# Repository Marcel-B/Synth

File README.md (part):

# Tonwerk Synth

Die beiden Browser-Synthesizer aus Tonwerk (YuE UI) als Plugins für Logic Pro: **Tonwerk Analog** und **Tonwerk FM**, jeder mit Delay und Hall und eigenen Werksklängen. Dazu kommen **Tonwerk DX** mit sechs Operatoren für den klassischen FM-Klang der Achtziger, der Wavetable-Synthesizer **Tonwerk Wavetable** für Dubstep-Bässe, der Granular-Synthesizer **Tonwerk Granular** für Klangwolken, **Tonwerk Physical**, der gezupfte, gestrichene, geblasene und angeschlagene Instrumente aus ihrer Physik nachrechnet, **Tonwerk Additiv**, der Klänge aus bis zu 64 einzelnen Obertönen zusammensetzt, **Tonwerk PD** mit Phasenverzerrung, der digitalen Synthese der Achtziger, der Sampler **Tonwerk Sampler** für eigene Samples, Loops und Vocal-Chops, **Tonwerk Bass**, ein Acid-Bass mit Slide und Accent, **Tonwerk Neuro**, ein monophoner Bass für Reese- und Neuro-Sounds aus Drum and Bass und Dubstep, **Tonwerk Expander**, ein achtstimmiger Analog-Synth nach Art der Expander-Module der Siebziger mit stufenlosem 12-dB-Multimode-Filter, die Drum-Machine **Tonwerk Groovebox** mit Step-Sequencer, **Tonwerk Drums**, ihre Klänge und acht weitere auf den Tasten der General-MIDI-Belegung, **Tonwerk Rig**, das eines dieser Instrumente mit bis zu sechs Effekten dahinter als einen Klang spielt, die Effekte **Chrome Glitch** für zerstückelte Gesangsspuren, **Tonwerk Distortion**, ein klassischer Gitarren-Verzerrer, **Tonwerk Robovox**, der eine Stimme wie einen Roboter singen lässt, **Tonwerk Vocoder**, der klassische Vocoder, bei dem die Stimme einen Synth spricht, den du mit Akkorden spielst, **Tonwerk Wobble**, Filter und Volume mit selbst gezeichneten LFO-Kurven im Tempo für Dubstep-Wobbles, **Tonwerk Tape**, eine leiernde, rauschende Bandmaschine für Lo-Fi, **Tonwerk Delay**, ein Ping-Pong-Delay im Songtempo mit Filtern im Feedback und Ducking, **Tonwerk Chorus**, Chorus, Ensemble, Flanger und Phaser in einem, **Tonwerk Glue**, ein Bus-Kompressor mit Sidechain und Pumpen im Songtempo, und **Tonwerk Shimmer**, ein Hall, dessen Fahne mit jedem Umlauf um ein Intervall nach oben steigt, **Tonwerk Filter**, ein Multimode-Filter mit Envelope Follower und LFO im Songtempo, **Tonwerk Stutter**, ein Beat Repeat, der Stücke im Songtempo wiederholt, **Tonwerk Multiband**, ein Drei-Band-Kompressor, abwärts und aufwärts, **Tonwerk Zone**, ein Kompressor für einen einstellbaren Frequenzbereich (dynamischer EQ, De-Esser), dessen Frequenz ein LFO wandern lassen kann, **Tonwerk Scope**, ein Oszilloskop mit Welle, Takten, Goniometer und Stimmgerät, **Tonwerk Rumble**, das aus der Kick selbst den rollenden Techno-Rumble darunter macht, **Tonwerk Reverb**, ein klassischer Hall mit Raum, Saal, Platte und Kathedrale, **Tonwerk Pump**, ein Sidechain-Compressor nur fürs Pumpen unter der Kick, **Tonwerk Spread**, der einen Klang aus der Mitte nach links und rechts verbreitert, ohne dass er in Mono etwas verliert, die MIDI-Effekte **Tonwerk Arp**, ein Arpeggiator und Step-Sequencer vor jedem Synth, und **Tonwerk LFO**, der per MIDI-Controller jeden Regler eines Tonwerk-Instruments bewegt (siehe unten). Klänge, die in Tonwerk auf der Instrumente-Seite gespeichert sind, lassen sich übernehmen und klingen hier wie dort.

**Sprache**: Alle Plugins und die App sprechen Deutsch oder Englisch. Auf einem deutschen System starten sie auf Deutsch, sonst auf Englisch. Der Schalter **DE | EN** oben im Fenster jedes Plugins wechselt die Sprache für alle Plugins zugleich; offene Fenster folgen nach spätestens einer Sekunde, die Knöpfe der iPad-App nach einem Neustart. Die Namen der Parameter in Logics Automation und im generischen Editor nehmen die Sprache beim Laden des Plugins an, also nach einem Neuladen des Projekts. Die Namen der Werksklänge bleiben deutsch, damit gespeicherte Projekte und Tonwerk Rig sie wiederfinden.

Logic lädt nur Audio Units, deshalb wird das Plugin als **Audio Unit** gebaut, dazu als VST3 (für andere Hosts) und als eigenständige App zum Ausprobieren ohne Logic.

## Zwei Plugins statt einem

Bis 0.3.0 waren beide Engines ein Plugin, **Tonwerk Synth**, mit einem Umschalter oben. Jetzt ist jede Engine ein eigenes Instrument: **Tonwerk Analog** (`aumu TwAn Bvlp`) und **Tonwerk FM** (`aumu TwFm Bvlp`). Jedes hat nur seine eigenen Regler (Logic zeigt bei der Automation also keine fremden mehr) und seine eigenen Werksklänge (siehe [Werksklänge](#werksklänge)).

Die aus Tonwerk oder Dateien übernommenen Klänge teilen sich beide Plugins (dieselbe `presets.json`); jedes zeigt im Menü nur die seiner Engine. Lädst du in Tonwerk Analog eine Datei mit FM-Klängen, landen sie im Menü von Tonwerk FM.

**Alte Projekte:** Tonwerk Synth bleibt installiert und lädt seine Projekte wie bisher, mit beiden Engines und den acht alten Werksklängen auf denselben Programmnummern (die neuen hängen dahinter). Es hat ebenfalls die neue Oberfläche. Für neue Spuren nimmst du Tonwerk Analog oder Tonwerk FM. Eine alte Spur ziehst du um, indem du in Tonwerk Synth **Speichern** drückst und die Datei im neuen Plugin mit **Datei laden** öffnest.

**Oberfläche:** alle Tonwerk-Plugins sehen jetzt aus wie Tonwerk Wavetable: fast schwarz, Gelb, Cyan und Rot im Neon-Look, Paneele mit abgeschnittener Ecke, Bildschirme mit Scanlines. Jede Hüllkurve zeigt ihre Form, Tonwerk FM zeichnet den gewählten Algorithmus (Träger gelb, Modulatoren cyan, die Rückkopplung an Operator 4) und schreibt über jede Operator-Hüllkurve, was der Operator gerade tut („TRÄGER“, „MOD → 1“). Werte stehen als ganze Zahlen mit Einheit da: Zeiten in ms, Pegel und Mengen in %, die Filter-Hüllkurve in Halbtönen (HT), langsame LFO-Raten mit einer Nachkommastelle.

## Was drin ist

**Analog**: zwei Oszillatoren (Sinus, Dreieck, Sägezahn, Rechteck/Puls) mit Oktave, Verstimmung und Pegel, Rauschen, Filter (Tiefpass, Hochpass, Bandpass) mit Resonanz, Keytracking und eigener Hüllkurve, Lautstärke-Hüllkurve, LFO auf Tonhöhe, Filter oder Lautstärke, frei oder im Songtempo. Der Puls hat eine Pulsbreite, die der LFO und beide Hüllkurven bewegen können (PWM).

**Wavefolder und Sample & Hold** gibt es nur im Plugin, nicht in Tonwerk. Der Wavefolder sitzt zwischen Oszillatoren und Filter. **Menge** treibt die Mischung bis zum Achtfachen und faltet alles über dem Vollpegel zurück, statt es abzuschneiden. **Symmetrie** verschiebt das Signal vor dem Falten, das bringt geradzahlige Obertöne. Mit **Hüllkurve** öffnet und schließt die Filter-Hüllkurve den Wavefolder. Sample & Hold nimmt in jedem Schritt einen neuen Zufallswert und hält ihn bis zum nächsten. **Filter** verschiebt damit den Cutoff um bis zu zwei Oktaven nach oben oder unten, **Tonhöhe** den Ton um bis zu eine Oktave. Das Tempo ist frei oder im Songtempo, und jede Note würfelt ihre eigene Folge. Beide stehen auf 0, solange du sie nicht aufdrehst, und Klänge aus Tonwerk laden mit beiden aus.

**FM**: vier Sinus-Operatoren in acht Algorithmen wie bei den 4-Operator-FM-Synths der Achtziger, Feedback auf Operator 4, eine Hüllkurve pro Operator, Anschlagsdynamik pro Operator, LFO auf Tonhöhe, Modulationsindex oder Lautstärke, frei oder im Songtempo.

**Effekte**: Delay mit Tiefpass in der Rückkopplung und Hall, beide als Send. Das Delay läuft frei oder im Songtempo.

**Tempo-Sync**: Mit **Sync** folgen LFO, Sample & Hold und Delay dem Tempo von Logic. Statt Hz oder Sekunden wählst du einen Notenwert von 4/1 bis 1/32, auch punktiert und triolisch. Ohne Host-Tempo (in der App) gelten 120 BPM. Der LFO beginnt wie in Tonwerk mit jeder Note neu. Er läuft also im Tempo, aber nicht auf den Schlag genau.

**Oszilloskop**: unten rechts neben der Tastatur, in beiden Plugins. Es zeigt die Wellenform dessen, was das Plugin gerade spielt, und steht bei einem gehaltenen Ton still.

16 Stimmen, Pitchbend ±2 Halbtöne, Sustain-Pedal. Jeder Regler ist ein Parameter, den Logic automatisieren kann und mit dem Projekt speichert. Jeder Drehregler lernt per Rechtsklick einen MIDI-Controller, etwa von [Tonwerk LFO](#tonwerk-lfo-midi-effekt-und-midi-lernen). Eine Tastatur unten im Fenster spielt das Plugin auch ohne MIDI-Keyboard an.

## Chrome Glitch (Effekt)

Ein Audio-Effekt aus demselben Repository, für eine Gesangsspur, deren „Sprach-Chrome“ versagt: Silben stottern („bo-bo-body“), die Stimme setzt kurz aus, wird digital zerbröselt und springt in der Tonhöhe. Er liegt in Logic unter **Audio-FX → Audio Units → b-velop → Chrome Glitch** und wird mit Tonwerk Synth zusammen gebaut, installiert und veröffentlicht.

Oben rechts sitzt ein kleiner **Monitor**: Solange die Stimme sauber ist, zeigt er „CHROME OK“. Bei jedem Glitch flimmert er mit zerrissenen Balken und Rauschen und zeigt „INTERFERENCE“ (Stottern), „NO SIGNAL“ (Aussetzer) oder „FROZEN“ (Einfrieren). Die Texte im Monitor sind bewusst englisch, wie die Anzeigen im Spiel. Auch Glitches, die kürzer als ein Bild sind, lassen ihn aufflackern.

Der Effekt arbeitet ohne Latenz auf dem, was gerade hereinkommt. An jedem Schritt des Rasters (im Songtempo) oder zu zufälligen Momenten (40–250 ms auseinander) würfelt er, ob etwas passiert:

- **Stottern**: Die letzten 10–200 ms (Standard 50 ms) werden mehrmals wiederholt. **Beschleunigen** macht jede Wiederholung kürzer, so wird die Silbe immer schneller. Ab der zweiten Wiederholung kann die Tonhöhe springen (**Pitch-Chance**, **Pitch-Bereich** bis ±24 Halbtöne).
- **Aussetzer**: Die Stimme fällt 20–300 ms ganz weg.
- **Bitcrusher**: Bei jedem Glitch voll (bis 4 Bit und 16-faches Downsampling), dazwischen nur leicht, mit der Stärke wachsend.
- **Einfrieren**: Hält die letzte Silbe in einer Schleife fest, solange es an ist. Für das letzte Wort, das hängen bleibt.
- **Tempo-Sync** und **Raster** (1/8, 1/16, 1/32) legen die Glitches aufs Raster. **Chaos** streut zusätzlich Glitches zwischen die Rasterpunkte und lässt die Stotterlänge schwanken, damit es nicht wie ein sauberer Stutter-Effekt klingt.
- **Glitch-Stärke** ist das Makro für die Automation: Auf 0 geht die Stimme unverändert durch, nach oben werden alle Chancen und der Crusher stärker. Für den letzten Chorus also die Stärke über die vier Zeilen hochziehen und am Ende **Einfrieren** einschalten. Die absolute Stille danach entsteht am einfachsten mit einem Schnitt in der Region.

Alle Übergänge werden über 1,5 ms überblendet, es knackt also nur, wo es soll.

**Seed** (0–999) macht die Glitches wiederholbar: Während Logic spielt, wird an jedem Schlag neu gewürfelt, aus dem Seed und der Nummer des Schlags. Ein Glitch gehört damit zu seiner Stelle im Song. Mit demselben Seed klingt der Chorus gleich, egal ob die Wiedergabe dort startet, am Anfang oder ob der ganze Song gebounct wird (ab dem ersten vollen Schlag nach dem Start; ein Stotterer braucht etwa 200 ms Vorlauf, weil er wiederholt, was davor lief). Passt eine Stelle nicht, gibt ein anderer Seed eine andere, wieder feste Folge. Der Seed lässt sich automatisieren, etwa ein Wert für den Chorus und ein anderer für die Bridge. Ohne laufenden Transport bleibt es zufällig.

**Presets** (Logics Programme, oben rechts im Menü und mit den Pfeilen): 13 Einstellungen in vier Gruppen, von **Dezent** (Leichtes Flackern, Wackelkontakt, Funkloch) über **Rhythmisch** (Achtel-Stotter, Sechzehntel-Roll, Stotter-Rampe, Zerhacker) und **Zerstört** (Kernschmelze, Cyberpsychose, Systemabsturz) bis **Klangeffekte** (Roboterstimme, Tonhöhen-Sprünge, Geisterecho mit 50 % Mix). Ein Preset setzt alle Regler, die es nicht nennt, auf ihren Standard zurück; Einfrieren und Seed bleiben also aus bzw. auf 0. Im Test bringt jedes auf einer Stimme in vier Takten Glitches, wird nicht lauter als die Stimme und höchstens 3 dB leiser (Aussetzer nehmen etwas weg).

**Getestet und ungetestet:** Unter Linux gebaut und getestet (Durchreichen bei Stärke 0, Stotterperiode, klickfreie Aussetzer und Tonhöhensprünge, Raster im Sync, Einfrieren, Crusher, Seed und Songposition, Zustand, Presets). `auval` für den Effekt läuft in der GitHub Action. In Logic ist er noch nicht gehört, die Presets nur auf einer künstlichen Stimme aus dem Test.

## Tonwerk Distortion (Effekt)

Der dritte Baustein aus diesem Repository: die Schaltung eines klassischen Verzerrer-Pedals, Stufe für Stufe nachgerechnet. Er liegt in Logic unter **Audio-FX → Audio Units → b-velop → Tonwerk Distortion** und wird mit den anderen beiden gebaut, installiert und veröffentlicht.

Oben zeigt ein Oszilloskop den Ausgang (gelb) über dem Eingang (cyan); so siehst du, wie Dist die Welle eckig macht. Die Regler sind die des Pedals, in derselben Reihenfolge:

- **Level**: die Lautstärke danach, −30 bis +12 dB. Bei 0 dB liegt eine voll verzerrte Note bei Tone in der Mitte um −6 dBFS.
- **Tone**: 0 % dunkel, 100 % hell. In der Mitte entsteht die typische Delle um 500 Hz (etwa 8 dB unter Bässen und Höhen), die das Pedal nach „Wand“ klingen lässt.
- **Dist**: 0 bis 100 %, wie das 100-kΩ-Poti im Pedal (Verstärkung der Op-Amp-Stufe 1- bis 22-fach). Auch auf 0 % zerrt das Pedal schon etwas, das macht der Transistor-Booster davor.
- **Eingang** gibt es am Pedal nicht: −24 bis +24 dB vor der Schaltung. Gerechnet wird mit 1,0 im Host = 1 V an der Eingangsbuchse, also etwa einer kräftig angeschlagenen Gitarre. Eine leise aufgenommene Gitarre oder ein Synth verzerrt mit mehr Eingang so, wie man es vom Pedal kennt.
- **Mix** gibt es am Pedal auch nicht: 0 % ist das trockene Signal, 100 % (Voreinstellung) nur die Verzerrung. Dazwischen liegt die Verzerrung unter dem Original, wie bei paralleler Verzerrung auf einem Bus: Anschlag und Bass bleiben, der Dreck kommt dazu. Das trockene Signal läuft durch dieselbe Überabtastung wie das verzerrte, damit beide genau gleich verzögert sind und sich nicht kammfiltern (im Test höchstens 0,2 dB Abweichung von 60 Hz bis 15 kHz).
- **Modus**: *Pedal* ist die Schaltung unten. Dazu kommen Kurven für elektronische Musik, jede mit Drive bis zu ihrer eigenen Höchstverstärkung und Tone als ±6-dB-Kippfilter um 700 Hz: *Röhre* (weich, geradzahlige Obertöne), *Clipper* (hartes Abschneiden für Kick und Drumbus), *Falter* (Sinus-Wavefolder, mehr Drive gibt mehr Falten) und *Gleichrichter* (Oktav-Fuzz). *Bitcrusher* rechnet wie ein alter Sampler: **Drive** nimmt die Bits von 16 (0 %) über etwa 6 (50 %) bis 2 (100 %) weg, leise Stellen werden zu Körnern und verstummen; **Crush** setzt die Samplerate von 48000 Hz (aus) bis 500 Hz herunter, die Spiegelfrequenzen klingeln dann metallisch mit. Der Bitcrusher macht nicht lauter, sein Pegel folgt dem Eingang. Ein Moduswechsel blendet über 20 ms über.

Was nachgebildet ist: Transistor-Booster (35 dB, Hochpass 33 Hz, weich in die Versorgung), Op-Amp-Stufe mit Dist-Poti, 72-Hz-Bassbeschnitt über C8 und 100 pF gegen das Zischeln, Rails eines 9-V-Single-Supply-Op-Amps (asymmetrisch, das gibt geradzahlige Obertöne), dann der Tiefpass 7,2 kHz und die zwei 1N4148 gegen Masse, aus der Shockley-Gleichung als Tabelle. Das ist das harte Clipping um ±0,6 V, das diesen Verzerrer von weicheren Overdrive-Pedalen unterscheidet. Danach die Tone-Blende aus Tiefpass 234 Hz und Hochpass 1063 Hz. Die Bauteilwerte stammen aus einer veröffentlichten Analyse der Originalschaltung. Weggelassen ist die Slew-Rate des Op-Amps: Der 7,2-kHz-Tiefpass verdeckt sie, und digital kostet sie mehr Aliasing, als sie bringt.

**CPU:** Die verzerrenden Stufen laufen vierfach überabgetastet, die Clipper zusätzlich mit Antiderivative-Antialiasing; was zurückfaltet, bleibt selbst bei einer 2,5-kHz-Note mit voller Verzerrung mehr als 60 dB unter dem Ton. Tone und Level laufen auf der normalen Rate. Stereo rechnet das Plugin im Test etwa 50-mal schneller als Echtzeit (rund 2 % eines Kerns), auf einer Mono-Spur nur einen Kanal, also die Hälfte. Die Überabtastung bringt eine Latenz von wenigen Samples, die das Plugin Logic meldet.

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
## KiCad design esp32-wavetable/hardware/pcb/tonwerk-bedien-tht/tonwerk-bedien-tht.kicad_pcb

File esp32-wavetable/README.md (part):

# Tonwerk Wavetable als Eurorack-Modul (ESP32-S3)

Konzept, Schaltplan-Skizze, Firmware-Grundgerüst, Stückliste und Frontplatte für ein 14-TE-Modul, das die Klangerzeugung von **Tonwerk Wavetable** (Plugin in diesem Repo, `wavetable/src/`) auf einem ESP32-S3 spielt.

Stand 2026-10-28. **Ein Modul ist gebaut und spielt** (bedrahtete Platinen v0.1, 27.10.2026); CV-Eingänge und V/Oct-Kalibrierung sind auf der Hardware noch nicht geprüft. Was geprüft ist, steht unter [Was getestet ist](#was-getestet-ist).

Mit anderen Firmwares spielt dasselbe Modul **Tonwerk Physical** (Physical Modeling): [Zweite Firmware](#zweite-firmware-tonwerk-physical), **Tonwerk PD** (Phase Distortion): [Dritte Firmware](#dritte-firmware-tonwerk-pd), **Tonwerk Granular** (Kornwolken aus neun Quellen): [Vierte Firmware](#vierte-firmware-tonwerk-granular), oder **Tonwerk Additiv** (64 Sinus-Teiltöne): [Fünfte Firmware](#fünfte-firmware-tonwerk-additiv), jede mit eigener Frontplatte.

Nachbauen: **[BAUANLEITUNG.md](BAUANLEITUNG.md)** führt Schritt für Schritt durch die bedrahtete Variante, vom Bestellen über Löten und erste Messungen bis zum Flashen und Kalibrieren. Auf der Website: [Bedienung](https://tonwerk.studio/modul/) und [Bauanleitung mit Bildern](https://tonwerk.studio/modul/bauanleitung.html).

## Die Idee in einem Absatz

Ein monophoner Wavetable-Oszillator mit eingebautem Filter und Hüllkurve. Er klingt wie eine Stimme des Plugins: dieselben zehn Tabellen (aus denselben Formeln berechnet), dieselben Warp-Modi, derselbe Filter (SVF 12/24 dB, Hochpass, Bandpass, Notch, Kamm, mit Drive), dieselbe Hüllkurve. Zwei Ausgänge: **OSC** ist der reine Oszillator (wie ein VCO, für externe Filter), **VOICE** ist dieselbe Stimme durch Filter und VCA. LFOs, Modulationsmatrix, Effekte und Polyphonie des Plugins fallen weg; das übernimmt im Modularsystem das Patchen.

## Bedienung

| Regler | Normal | WARP-Taste gehalten (Oszillator B) | FILTER-Taste gehalten |
|---|---|---|---|
| TUNE | ±2 Oktaven in Halbtönen | B: Transponierung ±24 Halbtöne | Attack 0,5 ms bis 2 s |
| FINE | ±50 Cent | B: Feinstimmung ±50 Cent | – |
| TABLE | Tabelle (10 Stück) | B: Tabelle, ganz links = B aus | – |
| POSITION | Position in der Tabelle | B: Position | Keytracking des Filters 0–100 % |
| WARP | Stärke des Warp | Unisono 1–4 Stimmen (A und B) | – |
| CUTOFF | 20 Hz bis 20 kHz | Unisono-Verstimmung 0–100 Cent | Hüllkurve → Cutoff, 0–6 Oktaven |
| RESO | Resonanz | Sub-Oszillator: Lautstärke, links = aus | Drive vor dem Filter |
| DECAY | Decay und Release, 5 ms bis 5 s | Sub: −1/−2 Oktaven, Sinus/Rechteck | Sustain (ab Werk 100 %) |
| POS CV | Abschwächer für POS-CV, Mitte = 0 | – | – |
| CUT CV | Abschwächer für CUTOFF-CV, rechts = 1 V/Okt | – | – |

- **WARP kurz drücken:** Warp-Modus weiter (aus, Sync, Bend, PWM, FM). LED 1 zeigt ihn: grau, cyan, gelb, magenta, rot. Nach dem Drehen an TABLE zeigt sie eine Sekunde lang die Tabelle (Farbkreis).
- **FILTER kurz drücken:** Filtermodus weiter (LP12, LP24, HP12, BP12, Notch, Kamm, aus). LED 2 zeigt ihn.
- **Taste halten und drehen** stellt die versteckte Ebene ein. Ein Regler übernimmt erst, wenn er den gespeicherten Wert erreicht („Pick-up“), damit nichts springt. Modi und versteckte Werte werden 3 s nach der letzten Änderung gespeichert.
- **Beide Tasten beim Einschalten halten:** V/Oct-Kalibrierung. 1,000 V an V/OCT (sonst nichts gesteckt), WARP drücken; 3,000 V anlegen, FILTER drücken. Grün = gespeichert, rot = unplausibel (alte Werte bleiben).
- **Nur WARP beim Einschalten halten:** Update über WLAN, siehe [Update über WLAN](#update-über-wlan). Bei den anderen Firmwares ist es dieselbe Taste (ERREGER, WELLE 1, QUELLE, KLANG A).

Buchsen: **V/OCT** (−1…+7 V, 0 V = C2), **GATE** (ab ca. 1,4 V; ohne Kabel ist das Gate dauerhaft an, das Modul läuft als Drone), **TABLE** (±5 V, 5 V = alle zehn Tabellen), **POS**, **WARP**, **CUTOFF** (±5 V), Ausgänge **OSC** und **VOICE** (±5 V).

## Zweite Firmware: Tonwerk Physical

Dieselben Platinen spielen mit einer anderen Firmware **Tonwerk Physical** (Plugin in diesem Repo, `physical/src/`): ein **Erreger** (Zupfen, Schlagen, Streichen, Blasen) bringt einen **Resonator** (Saite, Rohr geschlossen, Rohr offen, Stab, Glocke, Fell, Schale) zum Klingen, auf Wunsch durch Filter und Korpus. Bis zu vier Stimmen klingen übereinander aus, so wird aus einer Folge von Anschlägen ein Akkord oder eine Harfe. Eine eigene Frontplatte gehört dazu (unten), gedacht gelb mit schwarzer Schrift, damit man die Module im Rack auseinanderhält.

| Regler | Normal | ERREGER gehalten | RESON. gehalten |
|---|---|---|---|
| TUNE | ±2 Oktaven in Halbtönen | Attack von Bogen und Atem, 1 ms bis 2 s | Cutoff des Filters, 20 Hz bis 20 kHz |
| FINE | ±50 Cent | Decay von Bogen und Atem, 5 ms bis 5 s | Resonanz |
| HÄRTE (TABLE) | Härte des Anschlags: weich und dunkel bis hart und hell | Sustain von Bogen und Atem | Filter: aus, LP12, LP24, HP12, BP (ab Werk aus) |
| POSITION | Wo angeregt wird, vom Rand bis zur Mitte | Release von Bogen und Atem, 5 ms bis 5 s | Keytracking des Filters |
| KRAFT (WARP) | Bogendruck und Atem; bei Zupfen und Schlagen, wie stark angeschlagen wird | Rauschen (Kratzen, Luft) | Korpus: aus, Gitarre, Geige, Kiste, Resonanzboden |
| DÄMPF. (CUTOFF) | Dämpfung: wie viel schneller die hohen Obertöne verklingen | Dynamik: wie viel leiser ein schwacher Anschlag ist | Mix des Korpus |
| INHARM. (RESO) | Inharmonie: streckt die Obertöne (steife Saite, verstimmte Resonanzen) | – | – |
| DECAY | Abklingzeit des Resonators, 20 ms bis 20 s | Stimmen 1–4 (ab Werk 2) | Dämpfer nach dem Gate, 5 ms bis 60 s (ab Werk 60 s: der Ton klingt aus) |
| POS CV | Abschwächer für POS-CV, Mitte = 0 | – | – |
| DMP CV (CUT CV) | Abschwächer für die DÄMPF.-CV, Mitte = 0 | – | – |

- **ERREGER kurz drücken** (die WARP-Taste): Zupfen, Schlagen, Streichen, Blasen. LED 1: gelb, cyan, magenta, grün.
- **RESON. kurz drücken** (die FILTER-Taste): Saite, Rohr geschlossen, Rohr offen, Stab, Glocke, Fell, Schale. LED 2: gelb, orange, grün, cyan, blau, rot, magenta.
- Halten, Pick-up, Speichern und Kalibrieren wie oben. Beide LEDs leuchten mit dem neuesten Ton auf.
- **Anschlagen:** Eine steigende Flanke an GATE zupft oder schlägt eine neue Stimme an; fällt das Gate, senkt sich der Dämpfer auf die neueste (RESON.-Ebene, DECAY). Ist das Gate an (oder steckt kein Kabel), schlägt auch ein **Sprung an V/OCT** um mindestens einen halben Halbton an: ein Sequencer ohne Gate spielt so jede neue Note, ein Glide dagegen zieht nur die Tonhöhe. Die neueste Stimme folgt V/OCT, die älteren klingen in ihrer Tonhöhe weiter.
- **Streichen und Blasen** halten den Ton, solange das Gate an ist; ohne Gate-Kabel streicht der Bogen dauernd, das Modul ist eine Drone, KRAFT und DÄMPF. formen sie.

Buchsen: **V/OCT**, **GATE** wie oben; **HÄRTE**, **POS**, **KRAFT**, **DÄMPF.** (±5 V, je über den ganzen Weg ihres Reglers, POS und DÄMPF. über ihre Abschwächer); Ausgänge **ROH** (die Stimmen ohne Korpus, an der Stelle von OSC) und **KLANG** (mit Korpus, an der Stelle von VOICE). Ohne Korpus sind beide gleich.

## Dritte Firmware: Tonwerk PD

Eine dritte Firmware für dieselben Platinen: **Tonwerk PD** (Plugin in diesem Repo, `pd/src/`), Phase Distortion. Eine Kosinuswelle wird über eine gebogene Phase gelesen; je stärker die Biegung (DCW), desto mehr wird aus dem Sinus eine Säge, ein Rechteck, ein Puls oder eine Resonanz. Zwei **Linien** mit eigener Welle, eigener DCW- und Lautstärke-Hüllkurve, Ring- oder Rauschmodulation zwischen ihnen und der Chorus des Plugins, in Stereo an den beiden Ausgängen. Eine Stimme (das Plugin spielt mehrstimmig). Eine eigene Frontplatte gehört dazu.

| Regler | Normal | WELLE 1 gehalten | WELLE 2 gehalten |
|---|---|---|---|
| TUNE | ±2 Oktaven in Halbtönen | Attack der DCW-Hüllkurve, 1 ms bis 2 s | Verstimmung von Linie 2, ±50 Cent (ab Werk +7) |
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
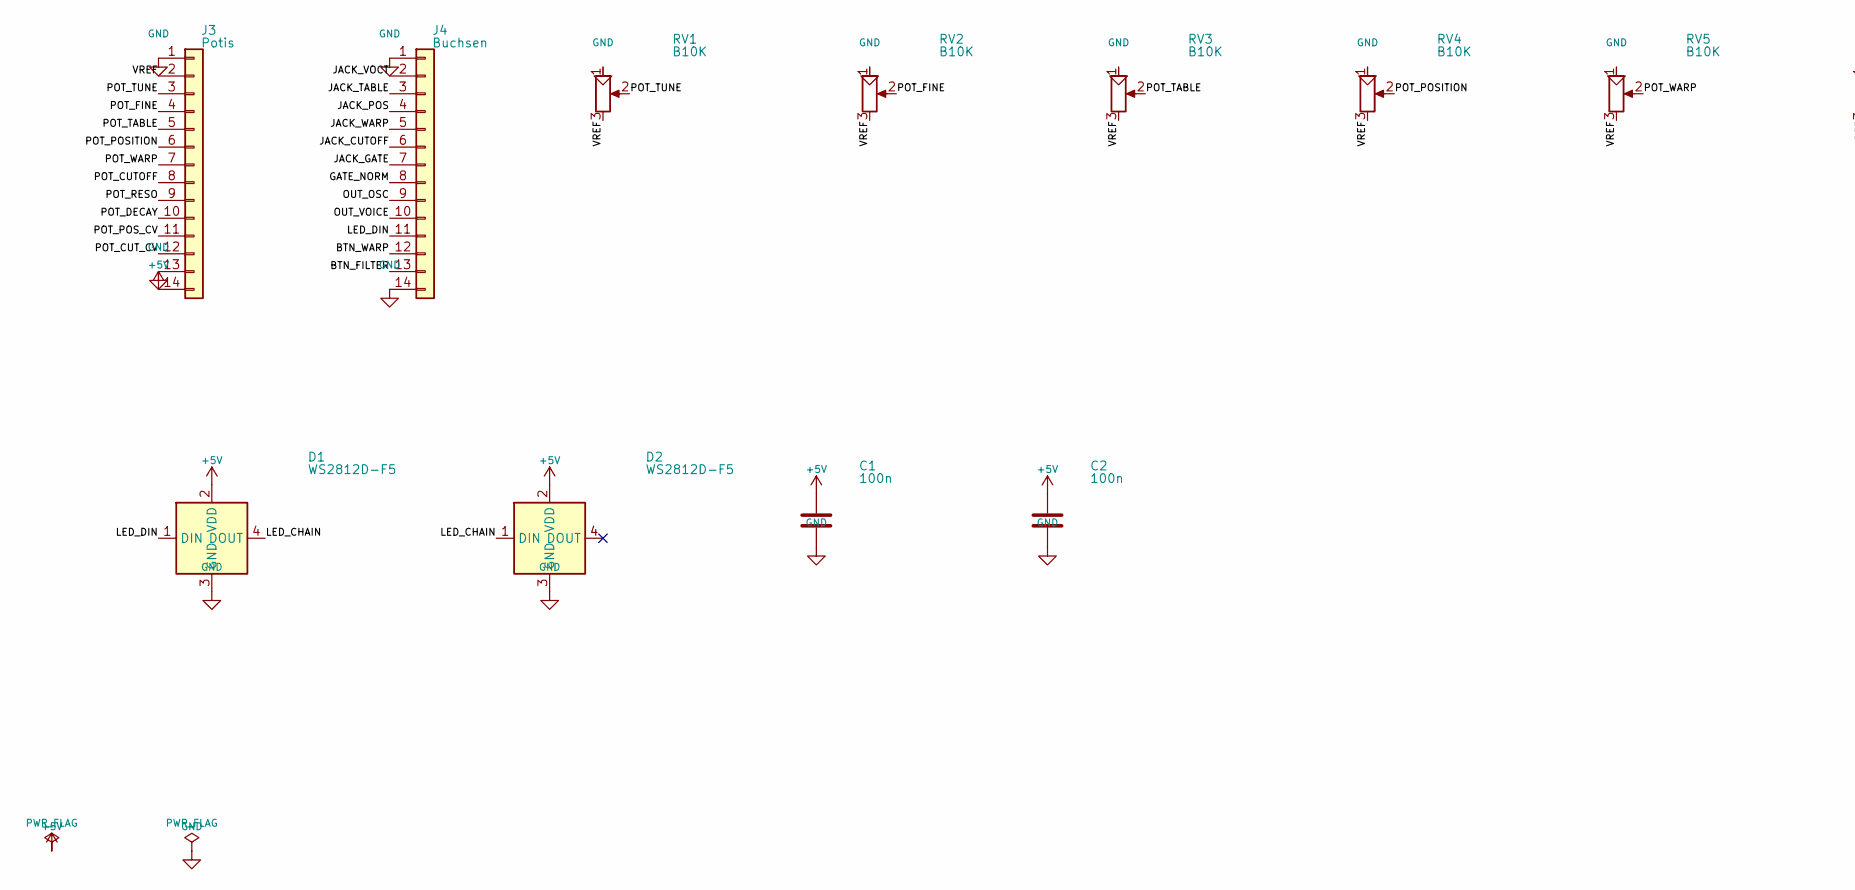
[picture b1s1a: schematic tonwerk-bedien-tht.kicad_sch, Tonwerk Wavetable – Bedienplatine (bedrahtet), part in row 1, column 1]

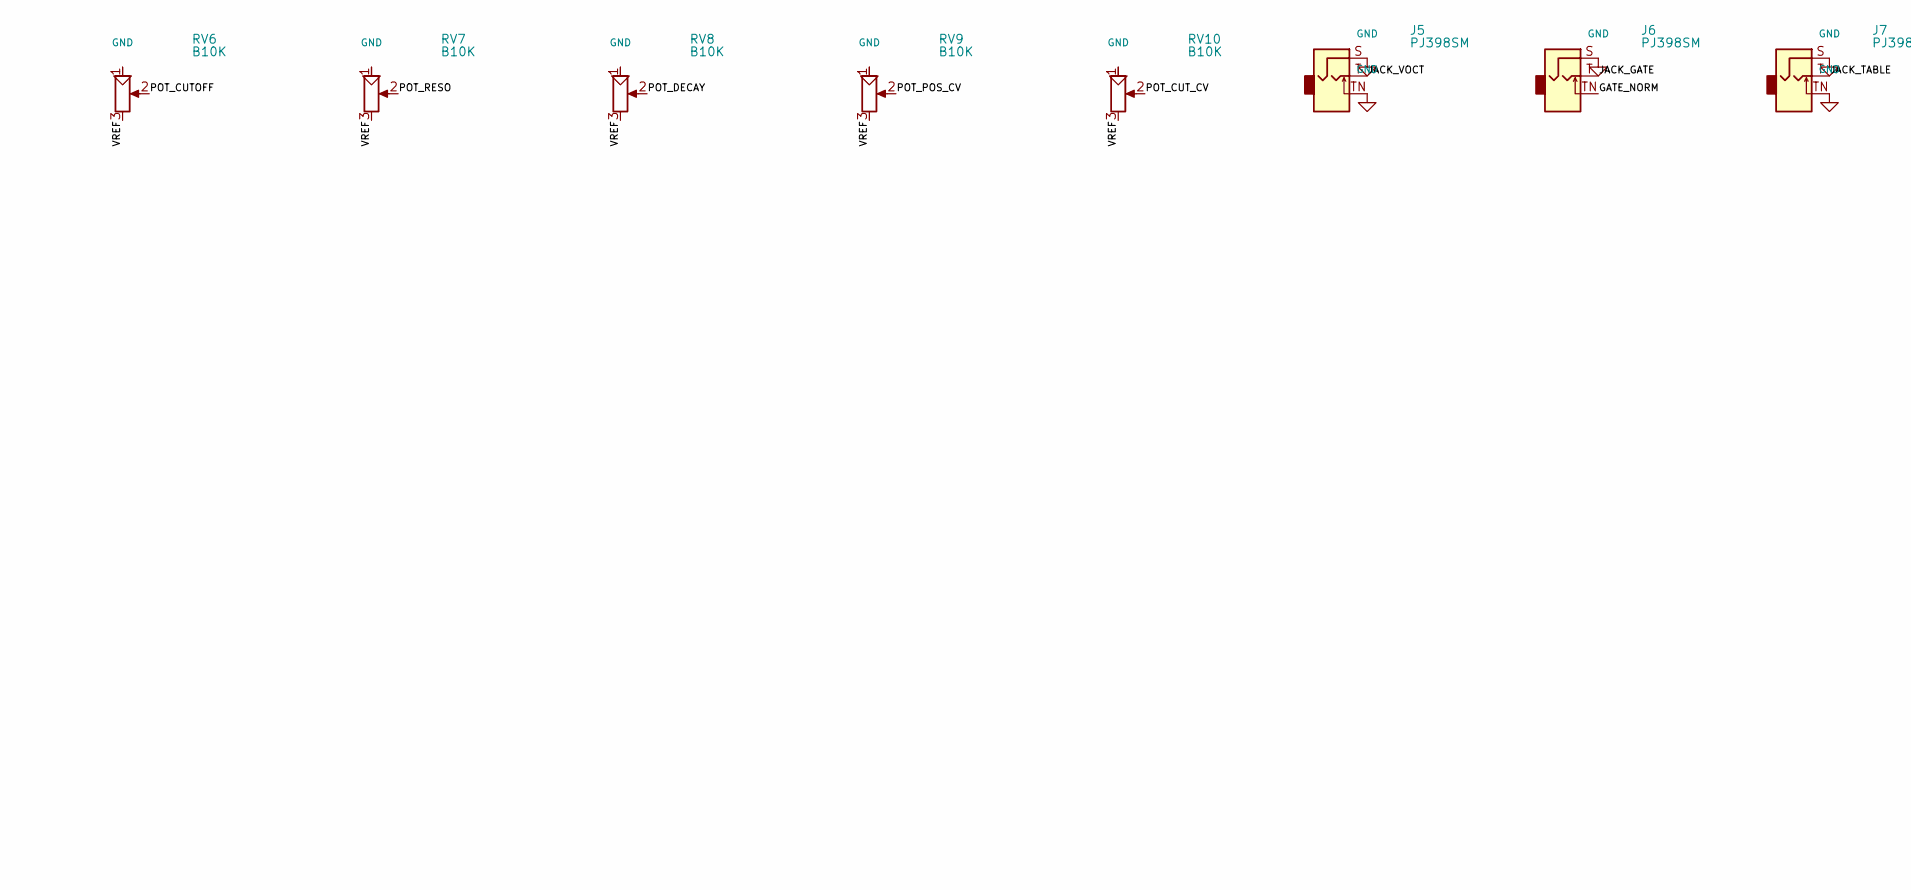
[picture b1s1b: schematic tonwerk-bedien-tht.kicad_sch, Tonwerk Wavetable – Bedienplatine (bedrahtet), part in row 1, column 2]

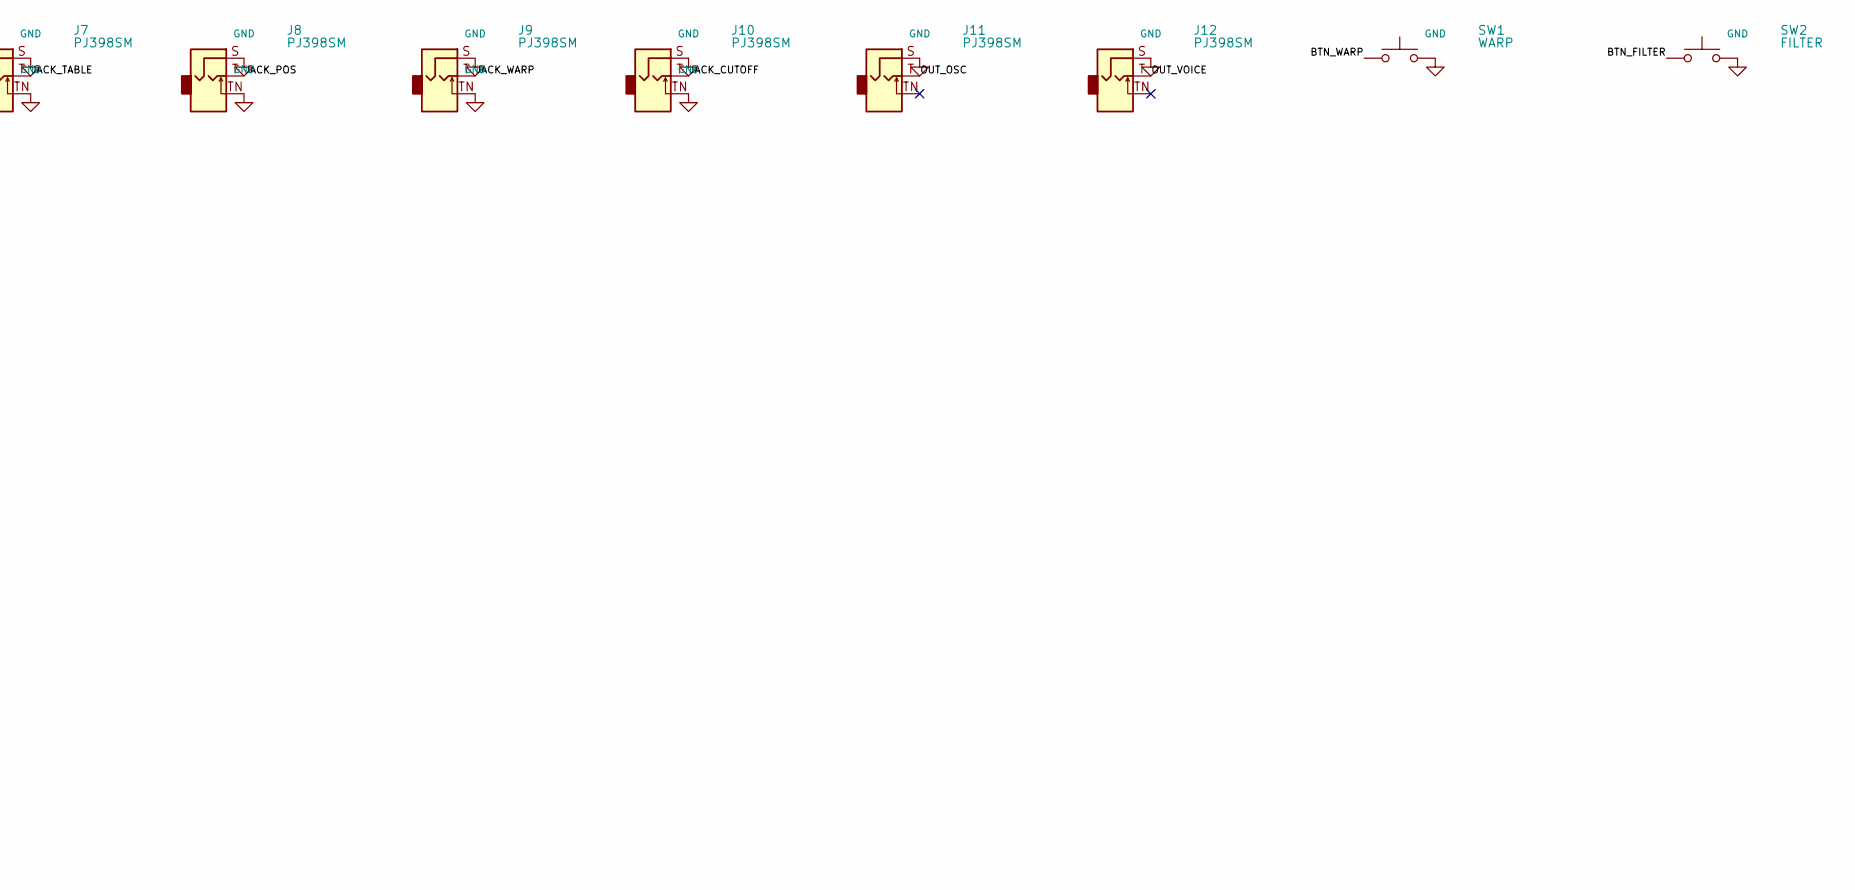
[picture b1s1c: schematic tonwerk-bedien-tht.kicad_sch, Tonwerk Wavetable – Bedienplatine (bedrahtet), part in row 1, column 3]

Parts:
C1, C2: 100n; C_Disc_D3.0mm_W2.0mm_P2.50mm
D1, D2: WS2812D-F5; LED_D5.0mm-4_RGB
J3: Potis; PinHeader_1x14_P2.54mm_Vertical
J4: Buchsen; PinHeader_1x14_P2.54mm_Vertical
J5, J6, J7, J8, J9, J10, J11, J12: PJ398SM; Jack_3.5mm_QingPu_WQP-PJ398SM_Vertical_CircularHoles
RV1, RV2, RV3, RV4, RV5, RV6, RV7, RV8, RV9, RV10: B10K; Potentiometer_Alpha_RD901F-40-00D_Single_Vertical
SW1: WARP; SW_PUSH_6mm_H13mm
SW2: FILTER; SW_PUSH_6mm_H13mm

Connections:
+5V: C1.1, C2.1, D1.2 (VDD), D2.2 (VDD), J3.14
BTN_FILTER: J4.13, SW2.1
BTN_WARP: J4.12, SW1.1
GATE_NORM: J4.8, J6.TN
GND: C1.2, C2.2, D1.3 (GND), D2.3 (GND), J3.1, J3.13, J4.1, J4.14, J5.S, J5.TN, J6.S, J7.S, J7.TN, J8.S, J8.TN, J9.S, J9.TN, J10.S, J10.TN, J11.S, J12.S, RV1.1, RV2.1, RV3.1, RV4.1, RV5.1, RV6.1, RV7.1, RV8.1, RV9.1, RV10.1, SW1.2, SW2.2
JACK_CUTOFF: J4.6, J10.T
JACK_GATE: J4.7, J6.T
JACK_POS: J4.4, J8.T
JACK_TABLE: J4.3, J7.T
JACK_VOCT: J4.2, J5.T
JACK_WARP: J4.5, J9.T
LED_CHAIN: D1.4 (DOUT), D2.1 (DIN)
LED_DIN: D1.1 (DIN), J4.11
OUT_OSC: J4.9, J11.T
OUT_VOICE: J4.10, J12.T
POT_CUTOFF: J3.8, RV6.2
POT_CUT_CV: J3.12, RV10.2
POT_DECAY: J3.10, RV8.2
POT_FINE: J3.4, RV2.2
POT_POSITION: J3.6, RV4.2
POT_POS_CV: J3.11, RV9.2
POT_RESO: J3.9, RV7.2
POT_TABLE: J3.5, RV3.2
POT_TUNE: J3.3, RV1.2
POT_WARP: J3.7, RV5.2
VREF: J3.2, RV1.3, RV2.3, RV3.3, RV4.3, RV5.3, RV6.3, RV7.3, RV8.3, RV9.3, RV10.3

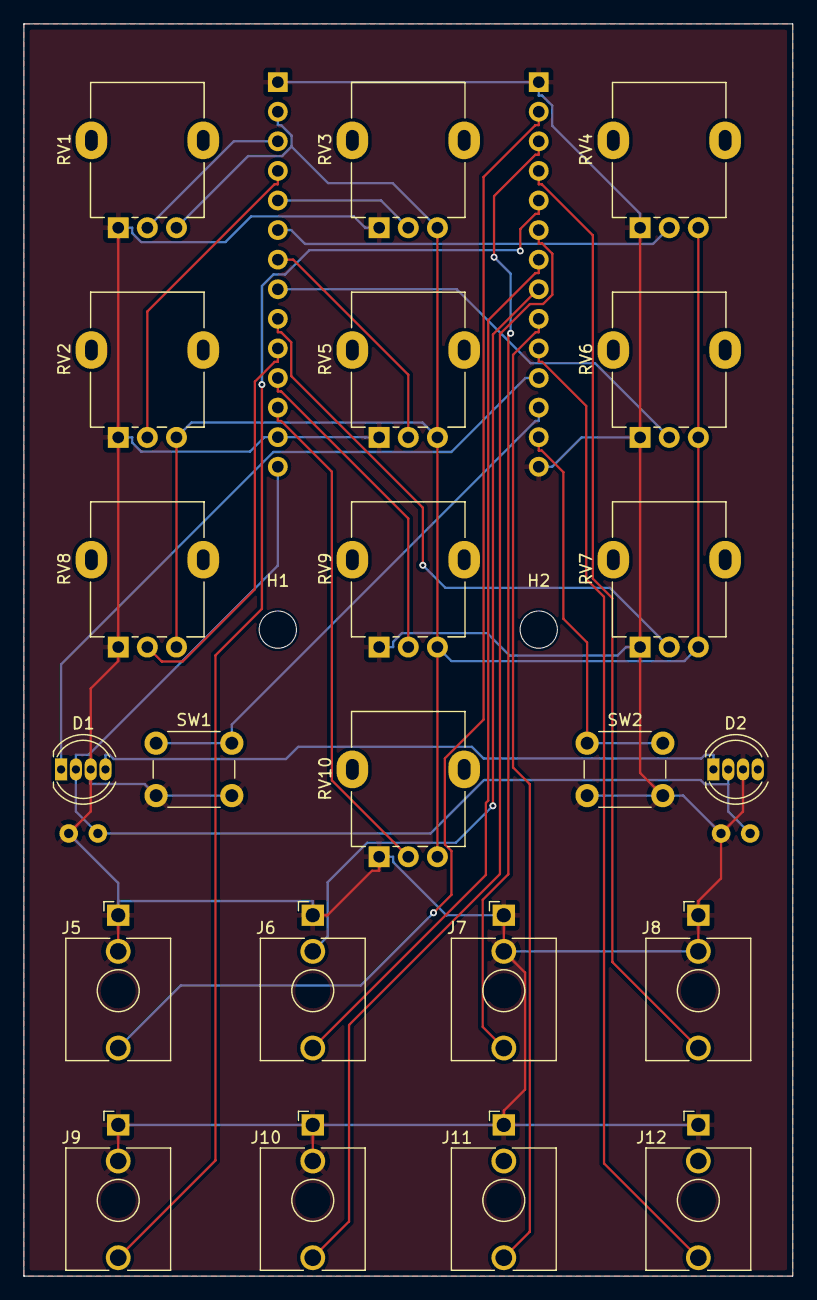
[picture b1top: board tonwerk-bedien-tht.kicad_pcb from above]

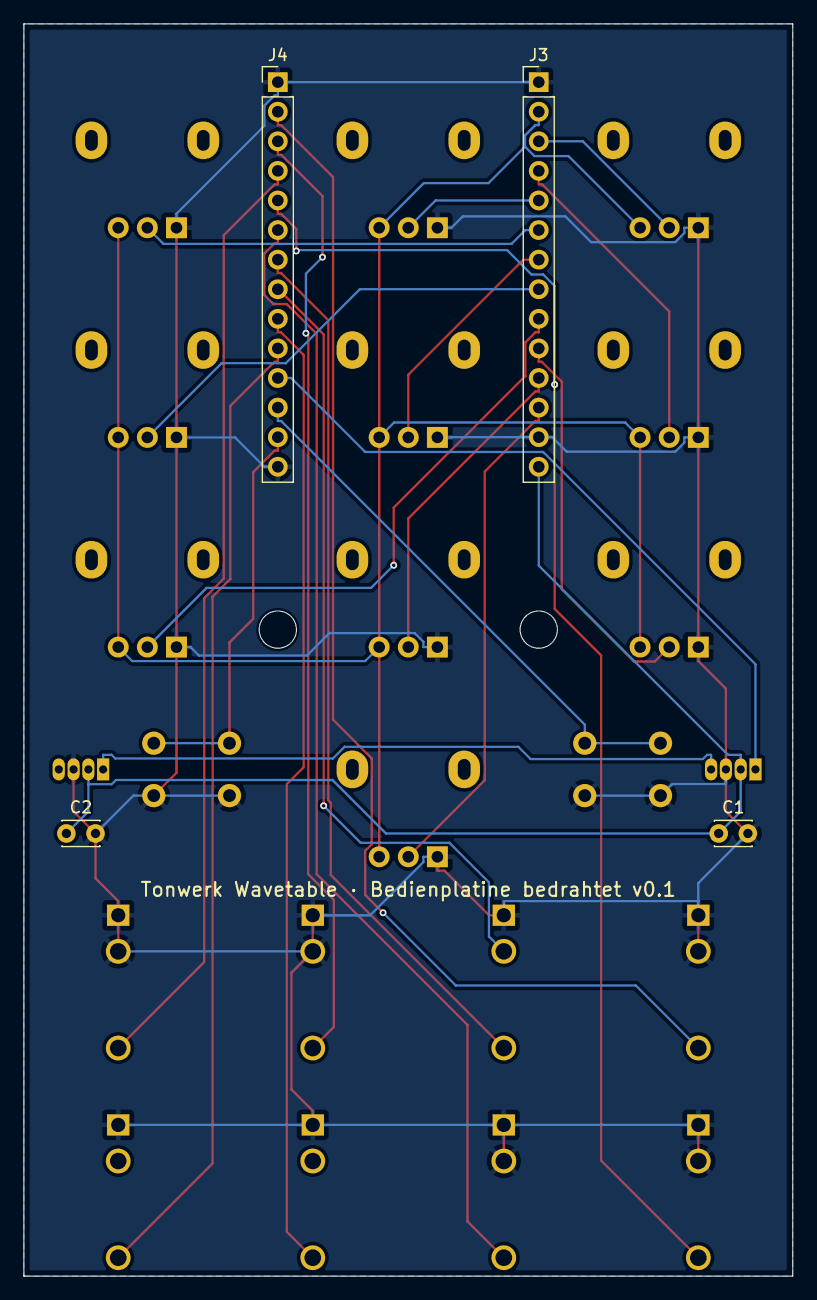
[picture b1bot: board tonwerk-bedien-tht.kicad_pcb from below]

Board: 2 copper layers, 66.0 x 107.5 mm, 28 parts (4 on the bottom side), 26 nets.

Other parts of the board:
H1, H2: M3; MountingHole_3.2mm_M3

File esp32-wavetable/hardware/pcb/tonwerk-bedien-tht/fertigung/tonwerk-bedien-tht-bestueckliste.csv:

Anzahl;Bauteil;Wert;Bauteile;Gehäuse;Seite;Hinweis
2;Keramikkondensator;100n;C1 C2;C_Disc_D3.0mm_W2.0mm_P2.50mm;hinten;
1;Stiftleiste;Buchsen;J4;PinHeader_1x14_P2.54mm_Vertical;hinten;Pin 1 oben
1;Stiftleiste;Potis;J3;PinHeader_1x14_P2.54mm_Vertical;hinten;Pin 1 oben
10;Poti;B10K;RV1 RV2 RV3 RV4 RV5 RV6 RV7 RV8 RV9 RV10;Potentiometer_Alpha_RD901F-40-00D_Single_Vertical;vorn;"RV1: TUNE; RV2: FINE; RV3: TABLE; RV4: POSITION; RV5: WARP; RV6: CUTOFF; RV7: RESO; RV8: DECAY; RV9: POS CV; RV10: CUT CV"
1;Taster;FILTER;SW2;SW_PUSH_6mm_H13mm;vorn;
8;Klinkenbuchse;PJ398SM;J5 J6 J7 J8 J9 J10 J11 J12;Jack_3.5mm_QingPu_WQP-PJ398SM_Vertical_CircularHoles;vorn;"J5: V/OCT; J6: GATE; J7: TABLE; J8: POS; J9: WARP; J10: CUTOFF; J11: OSC; J12: VOICE"
1;Taster;WARP;SW1;SW_PUSH_6mm_H13mm;vorn;
2;RGB-LED;WS2812D-F5;D1 D2;LED_D5.0mm-4_RGB;vorn;

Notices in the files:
README.md:
Bis Version 0.5.0 (Quelltext bis Commit `c9ab322`, 17.10.2026) stand das Projekt unter der AGPL-3.0 mit Namensnennung; wer diese Fassungen hat, darf sie weiter unter der AGPL nutzen.
Die Plugins nutzen [JUCE](https://juce.com) 8, das unter AGPLv3 oder einer kommerziellen Lizenz steht.
esp32-wavetable/README.md:
Felucca-Code ist hier nicht enthalten (GPL); alles stammt aus Tonwerk Wavetable, Tonwerk Physical, Tonwerk PD, Tonwerk Granular und Tonwerk Additiv und ist neu geschrieben.
